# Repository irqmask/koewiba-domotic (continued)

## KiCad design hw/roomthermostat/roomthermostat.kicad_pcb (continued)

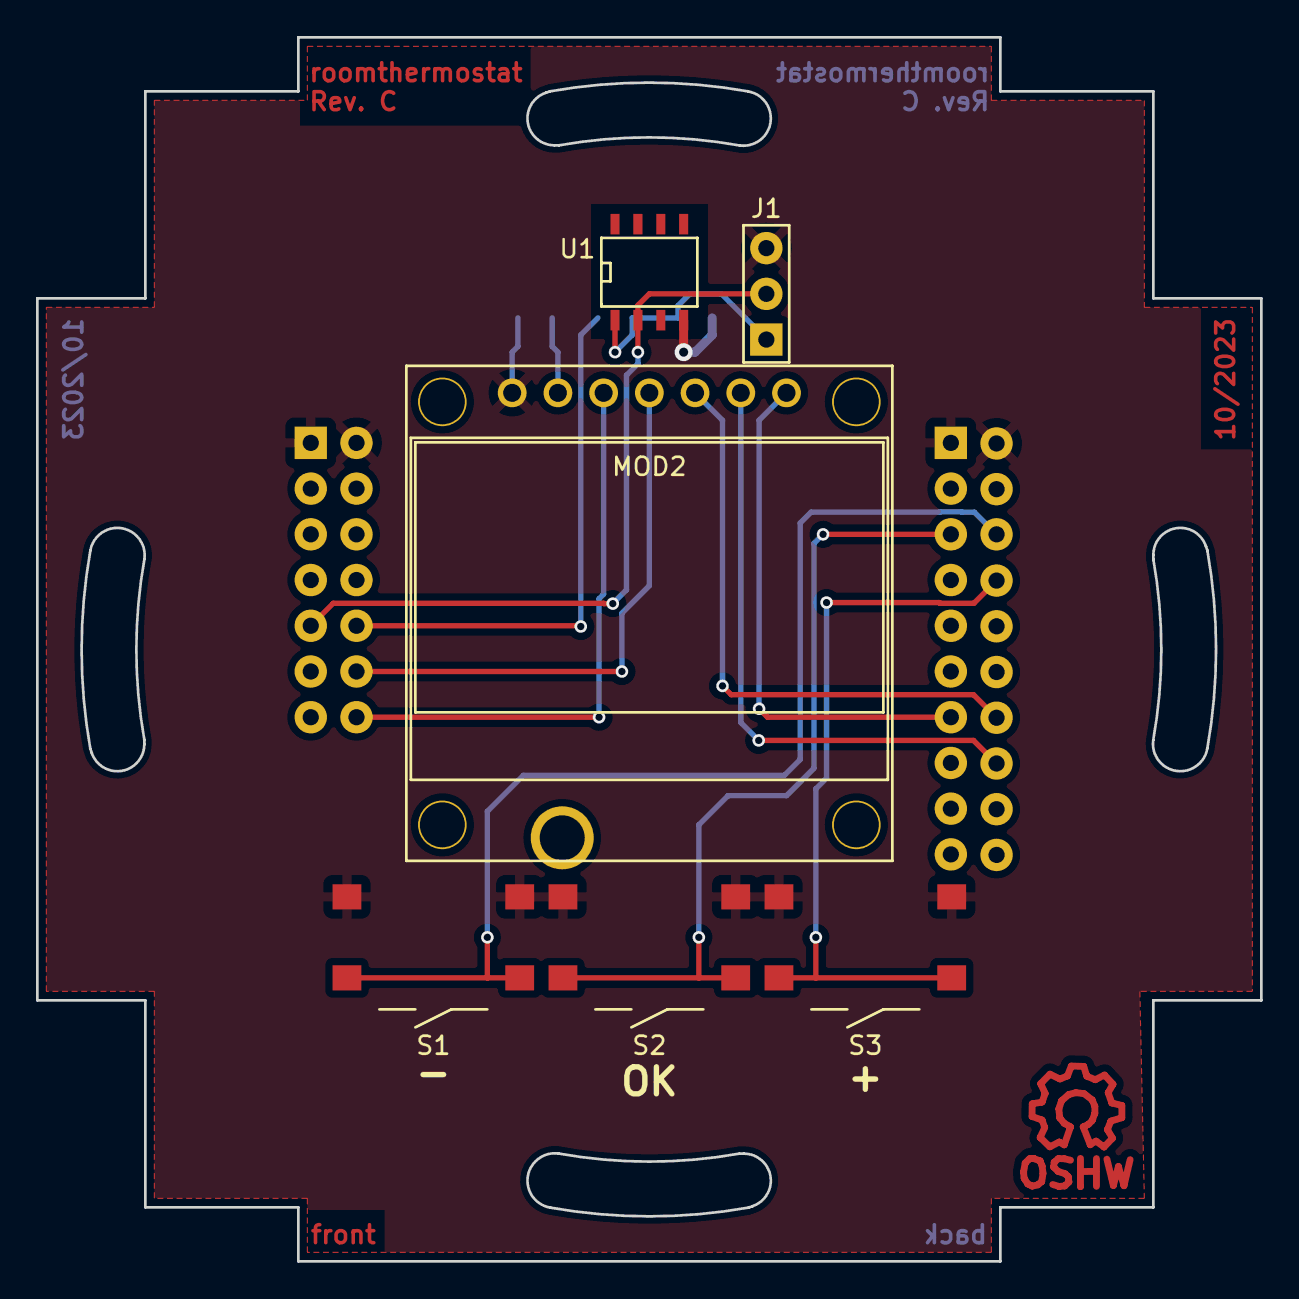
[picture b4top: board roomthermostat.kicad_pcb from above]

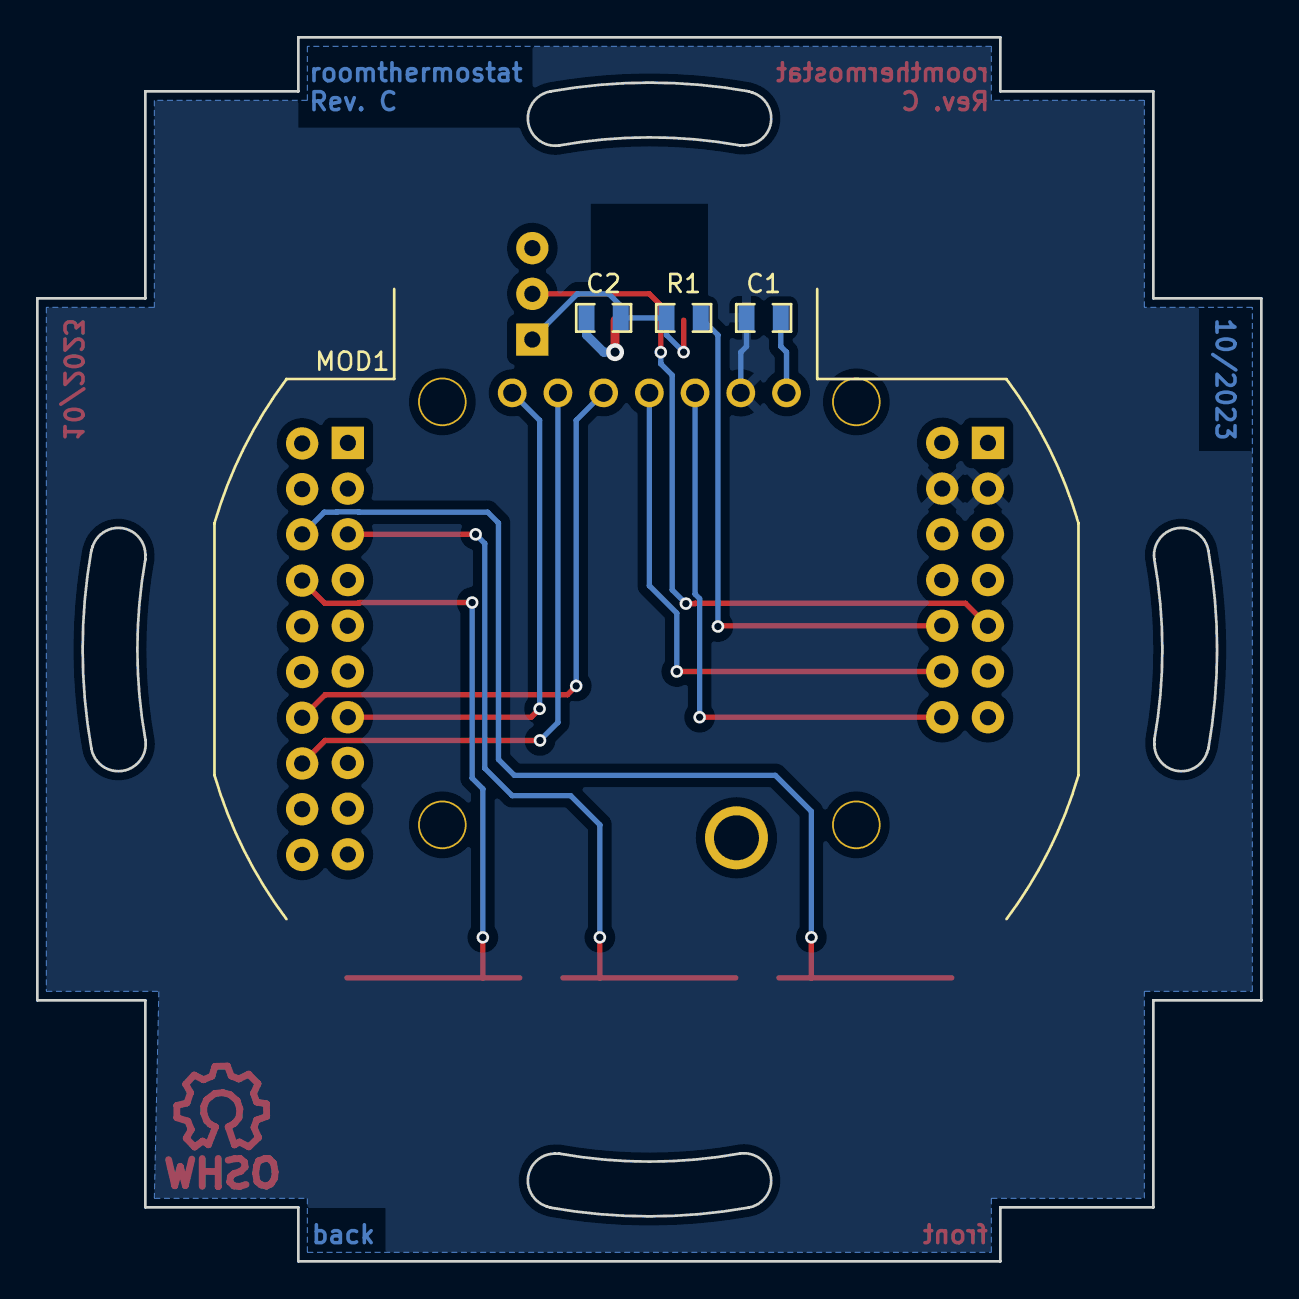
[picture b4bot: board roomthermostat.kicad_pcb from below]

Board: 2 copper layers, 68.0 x 68.0 mm, 11 parts (4 on the bottom side), 13 nets.

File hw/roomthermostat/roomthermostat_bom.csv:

"ID";"Bezeichner";"Gehäuse";"Stückzahl";"Bezeichnung";"Anbieter und Referenz";
1;"MOD2";"GraphDisplay_1_OLED_27x27,5mm_030072BA";1;"Graphic-OLED-Display_4wireSPI";;;
2;"U1";"SO8E";1;"TSIC206_SOIC8";;;
3;"S1,S2,S3";"PushButton_SPST_SMD_JTP-1138_BacksideMount";3;"PushButton_SPST_NO";;;
4;"LOGO1";"Symbol_OSHW-Logo_Copper";1;"OPEN_HARDWARE_1";;;
5;"J1";"HEADER_3x1";1;"CONN_3X1";;;
6;"C1,C2";"C_0805";2;"100nF";;;
7;"R1";"R_0805";1;"220";;;
8;"MOD1";"bus-module_atmega328";1;"bus-module_atmega328_revB";;;

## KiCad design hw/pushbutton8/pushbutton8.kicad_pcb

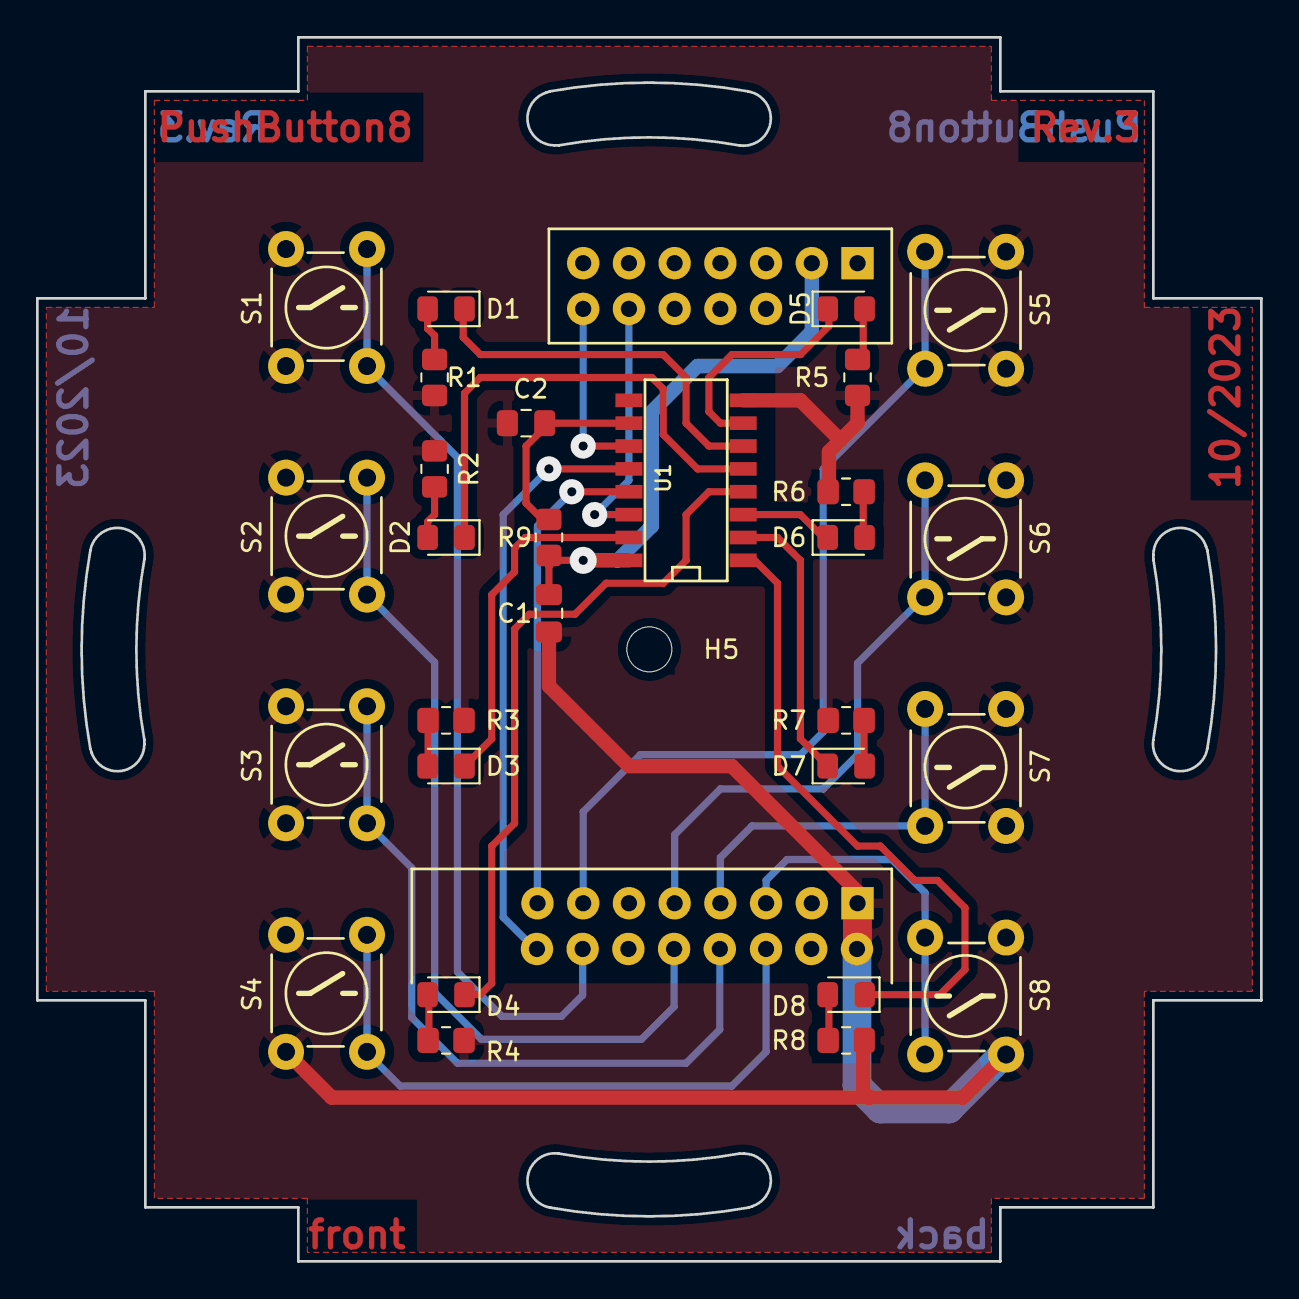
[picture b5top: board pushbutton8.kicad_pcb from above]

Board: 2 copper layers, 68.0 x 68.0 mm, 30 parts (1 on the bottom side), 31 nets.

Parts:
C1, C2: 100nF; C_0805_2012Metric_Pad1.18x1.45mm_HandSolder
D1, D2, D3, D4, D5, D6, D7, D8: LED; LED_0805_2012Metric_Pad1.15x1.40mm_HandSolder
H5: HOLE; MountingHole_2.5mm
MOD1: bus-module_atmega328
R1, R2, R3, R4, R5, R6, R7, R8: R; R_0805_2012Metric_Pad1.20x1.40mm_HandSolder
R9: 4k7; R_0805_2012Metric_Pad1.20x1.40mm_HandSolder
S1, S2, S3, S4, S5, S6, S7, S8: TASTER 3301; PHAP3301
U1: 74HC595; SO16N

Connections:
unnamed: C1.1, MOD1.23 (VCC), R9.1, U1.16 (VCC)
unnamed: C1.2, C2.2, MOD1.1 (GND), MOD1.2 (GND), R1.2, R2.2, R3.2, R4.2, R5.2, R6.2, R7.2, R8.2, S1.1, S2.1, S3.1, S4.1, S5.1, S6.1, S7.1, S8.1, U1.8 (GND)
unnamed: C2.1, R9.2, U1.10 (~MR)
unnamed: D1.1 (A), U1.6 (Q6)
unnamed: D1.2 (C), R1.1
unnamed: D2.1 (A), U1.5 (Q5)
unnamed: D2.2 (C), R2.1
unnamed: D3.1 (A), U1.15 (Q0)
unnamed: D3.2 (C), R3.1
unnamed: D4.1 (A), U1.4 (Q4)
unnamed: D4.2 (C), R4.1
unnamed: D5.1 (A), U1.7 (Q7)
unnamed: D5.2 (C), R5.1
unnamed: D6.1 (A), U1.3 (Q3)
unnamed: D6.2 (C), R6.1
unnamed: D7.1 (A), U1.2 (Q2)
unnamed: D7.2 (C), R7.1
unnamed: D8.1 (A), U1.1 (Q1)
unnamed: D8.2 (C), R8.1
unnamed: MOD1.5 (PC1), S8.2
unnamed: MOD1.6 (PC0), S4.2
unnamed: MOD1.7 (PC3), S7.2
unnamed: MOD1.8 (PC2), S3.2
unnamed: MOD1.9 (PC5), S6.2
unnamed: MOD1.10 (PC4), S2.2
unnamed: MOD1.13 (PD4), S5.2
unnamed: MOD1.14 (PD3), S1.2
unnamed: MOD1.15 (PD6), U1.13 (~OE)
unnamed: MOD1.16 (PD5), U1.12 (STCLK)
unnamed: MOD1.32 (MOSI), U1.14 (SER)
unnamed: MOD1.34 (SCK), U1.11 (SRCLK)

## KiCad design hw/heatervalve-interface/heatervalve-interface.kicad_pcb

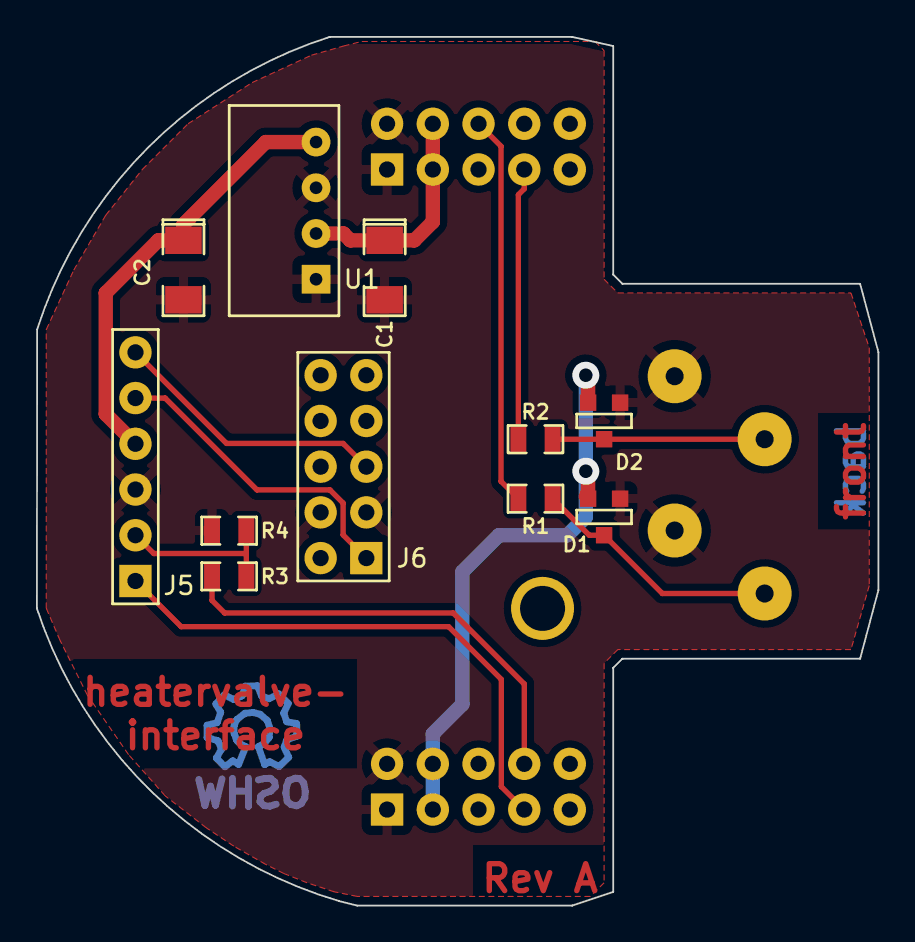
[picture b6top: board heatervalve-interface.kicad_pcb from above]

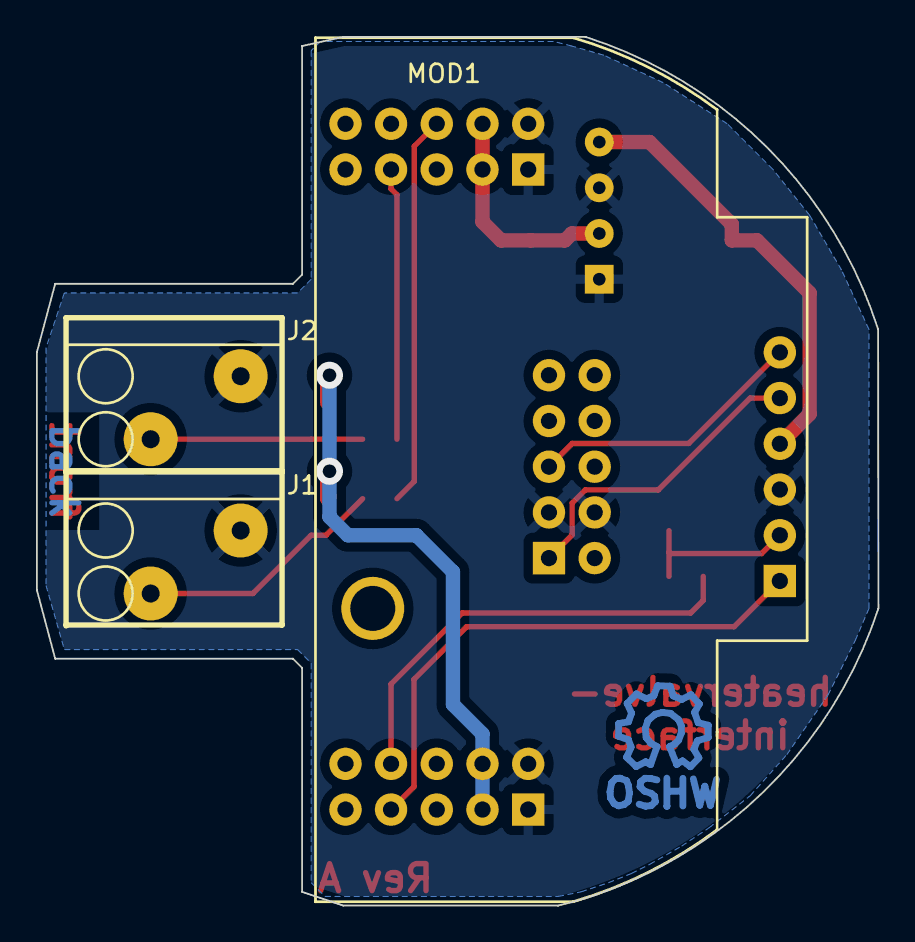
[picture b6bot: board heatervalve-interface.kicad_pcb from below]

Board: 2 copper layers, 46.8 x 48.3 mm, 15 parts (4 on the bottom side), 13 nets.

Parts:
C1: 470µF; CP_1206
C2: 100µF; CP_1206
D1, D2: BAT54S; SOT23-3
J1, J2: CONN_2X1; WAGO250-202
J5: CONN_6X1; HEADER_6x1
J6: CONN_5X2; HEADER_5x2
LOGO1: OPEN_HARDWARE_1; Symbol_OSHW-Logo_Copper
MOD1: bus-module_attiny1634_revB; bus-module_attiny1634
R1, R2, R3: 4k7; R_0805
R4: 9k1; R_0805
U1: AM1S-2403; AM1S-XXXX_SIL4

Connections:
+3.3V: C2.1, J5.4, U1.4 (VOUT+)
+5V: D1.2, D2.2, MOD1.13 (VCC), MOD1.14 (VCC)
+24V: C1.1, MOD1.3 (24V), MOD1.4 (24V), U1.2 (VIN+)
/RXD: J5.1, MOD1.17 (MISO)
/STM8_RST: J5.5, J6.1
/TXD: MOD1.18 (MOSI), R3.1
GND: C1.2, C2.2, D1.1, D2.1, J1.2, J2.2, J5.3, J6.3, J6.4, MOD1.1 (GND), MOD1.2 (GND), MOD1.11 (GND), MOD1.12 (GND), R4.1, U1.1 (VIN-), U1.3 (VOUT-)
unnamed: D1.3, J1.1, R1.1
unnamed: D2.3, J2.1, R2.1
unnamed: J5.2, R3.2, R4.2
unnamed: J5.6, J6.5
unnamed: MOD1.6 (PA1), R1.2
unnamed: MOD1.7 (PA2), R2.2

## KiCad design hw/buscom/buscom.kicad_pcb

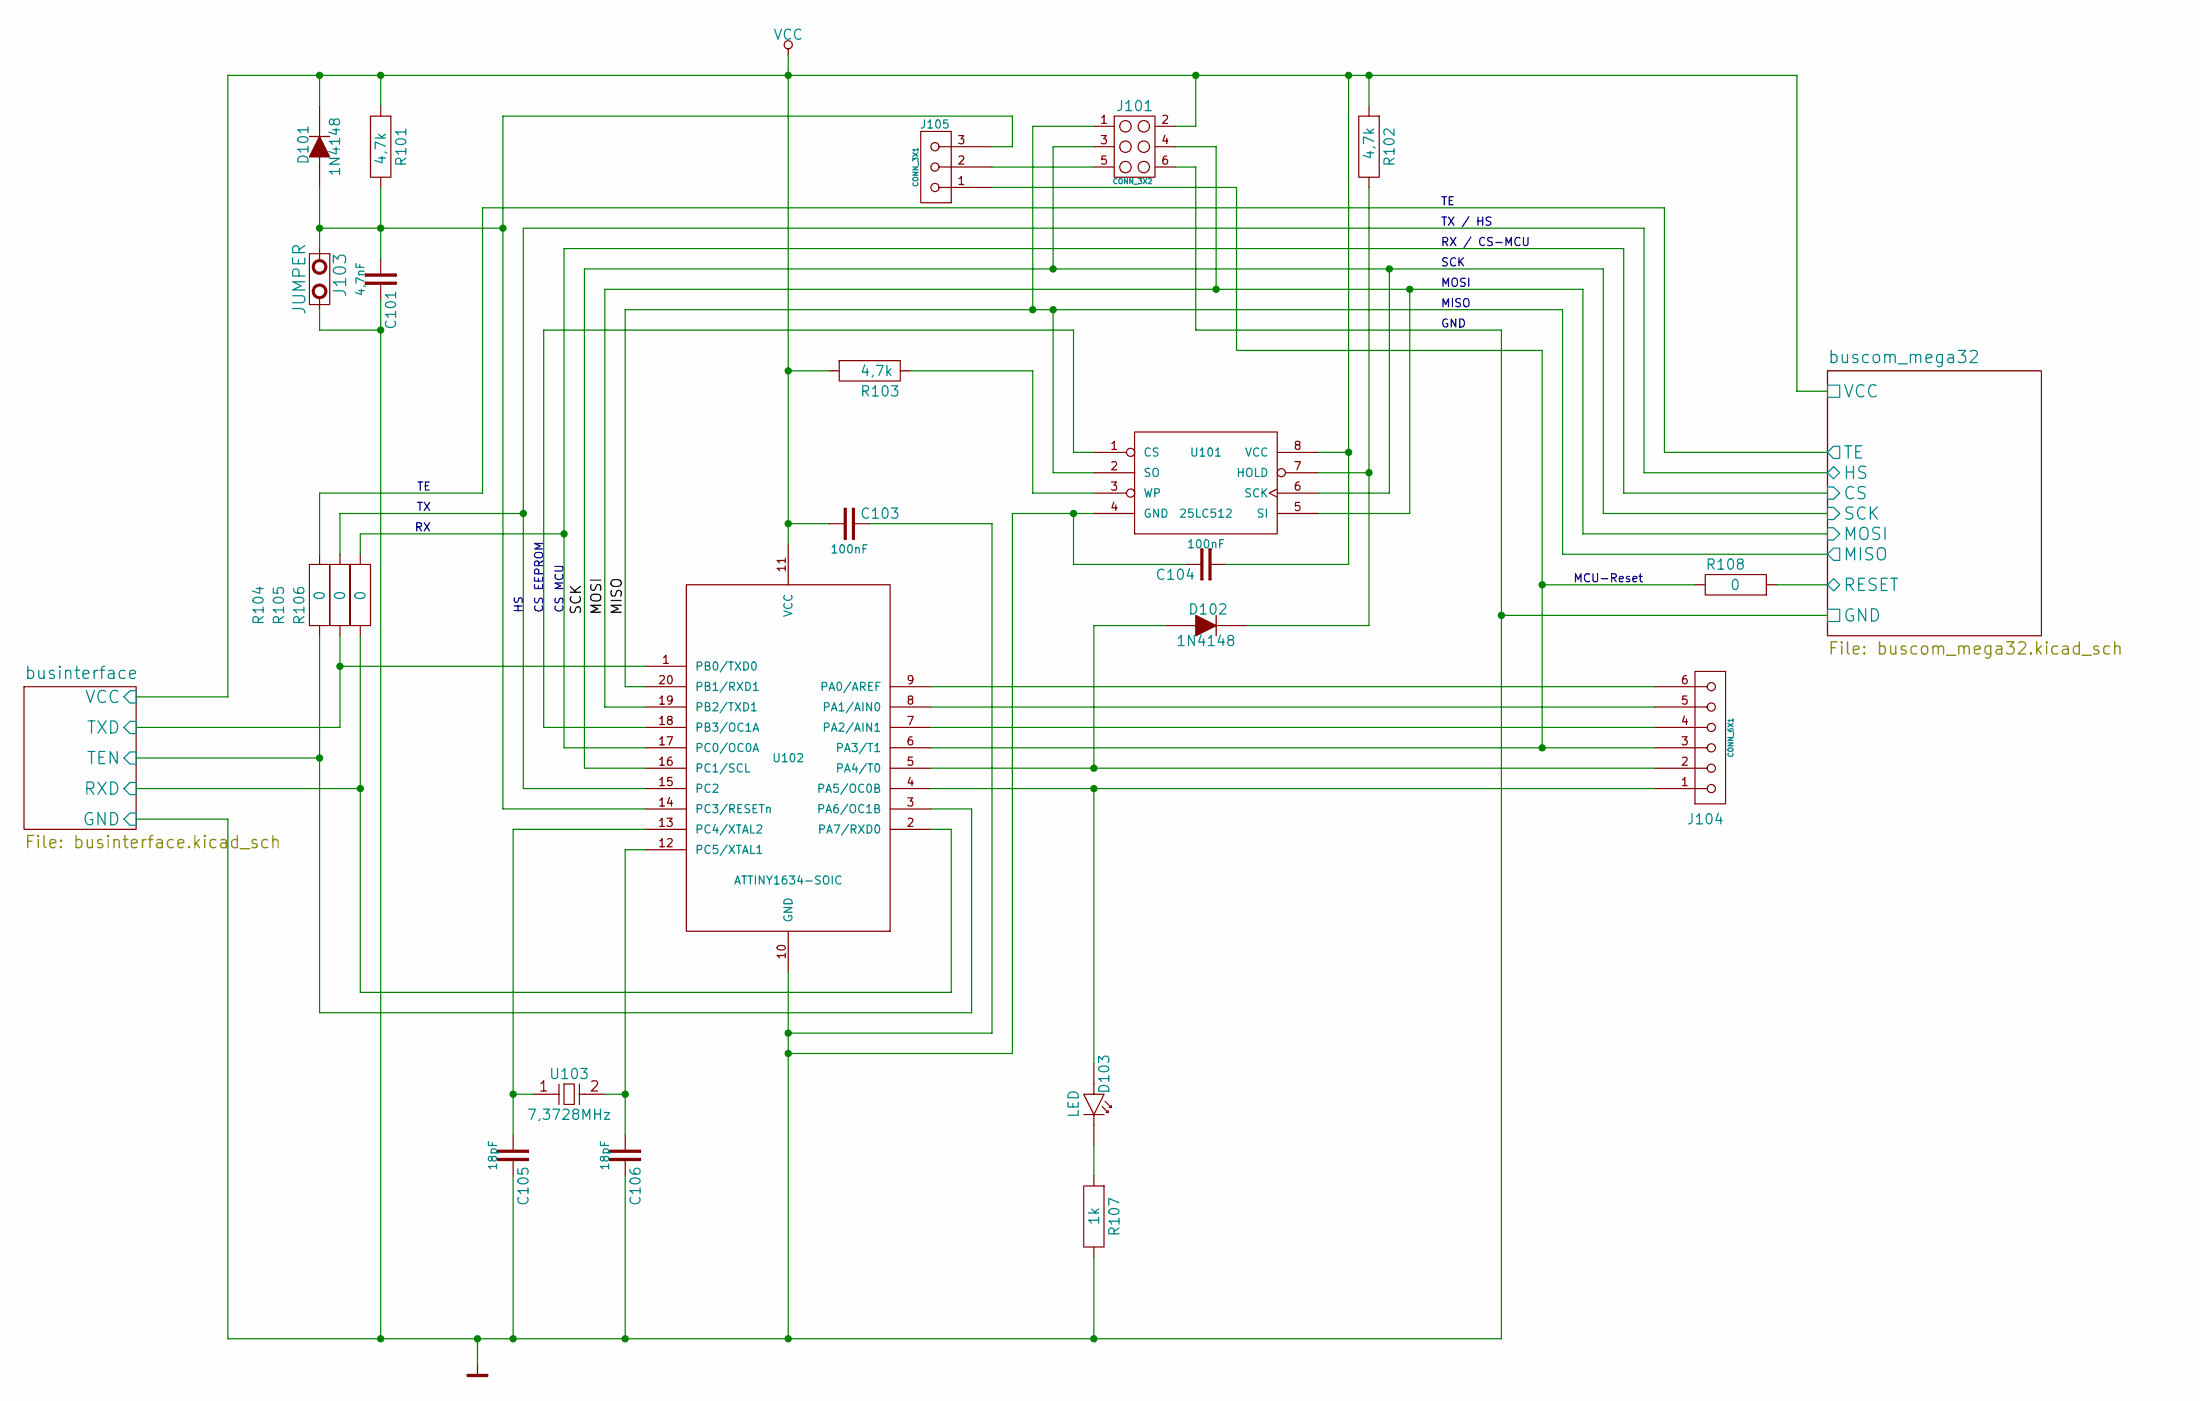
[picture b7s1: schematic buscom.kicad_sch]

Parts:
C101: 4,7nF
C103, C104: 100nF
C105, C106: 18pF
D101, D102: 1N4148
D103: LED
J101: CONN_3X2
J103: JUMPER
J104: CONN_6X1
J105: CONN_3X1
R101, R102, R103: 4,7k
R104, R105, R106, R108: 0
R107: 1k
U101: 25LC512; SO8N
U102: ATTINY1634-SOIC; SO20L
U103: 7,3728MHz

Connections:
/buscom_1: C101.2, C103.2, C104.2, C105.2, C106.2, J101.6, J103.2, R107.2, U101.4 (GND), U102.10 (GND); also elsewhere on the board
/buscom_3: R108.1; also elsewhere on the board
/buscom_7: J101.1, U101.2 (SO), U102.20 (PB1/RXD1); also elsewhere on the board
/buscom_8: J101.3, U101.6 (SCK), U102.16 (PC1/SCL); also elsewhere on the board
/buscom_9: J101.4, U101.5 (SI), U102.19 (PB2/TXD1); also elsewhere on the board
/buscom_36: R104.1; also elsewhere on the board
/buscom_37: R105.1, U102.15 (PC2); also elsewhere on the board
/buscom_38: R106.1, U102.17 (PC0/OC0A); also elsewhere on the board
/businte2: C103.1, C104.1, D101.2 (C), J101.2, R101.1, R102.1, R103.1, U101.8 (VCC), U102.11 (VCC); also elsewhere on the board
/businte42: R104.2, U102.3 (PA6/OC1B); also elsewhere on the board
/businte43: R105.2, U102.1 (PB0/TXD0); also elsewhere on the board
/businte44: R106.2, U102.2 (PA7/RXD0); also elsewhere on the board
unnamed: J101.5, J105.2
unnamed: J104.3, J105.1, R108.2, U102.6 (PA3/T1)
unnamed: D102.1 (A), J104.2, U102.5 (PA4/T0)
unnamed: U101.1 (CS), U102.18 (PB3/OC1A)
unnamed: C106.1, U102.12 (PC5/XTAL1), U103.2
unnamed: J104.6, U102.9 (PA0/AREF)
unnamed: J104.5, U102.8 (PA1/AIN0)
unnamed: J104.4, U102.7 (PA2/AIN1)
unnamed: D102.2 (C), R102.2, U101.7 (HOLD)
unnamed: R103.2, U101.3 (WP)
unnamed: D103.2 (C), R107.1
unnamed: D103.1 (A), J104.1, U102.4 (PA5/OC0B)
unnamed: C101.1, D101.1 (A), J103.1, J105.3, R101.2, U102.14 (PC3/RESETn)
unnamed: C105.1, U102.13 (PC4/XTAL2), U103.1

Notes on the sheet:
CS EEPROM
MOSI
SCK
MCU-Reset
CS MCU
GND
MISO
RX / CS-MCU
TX / HS

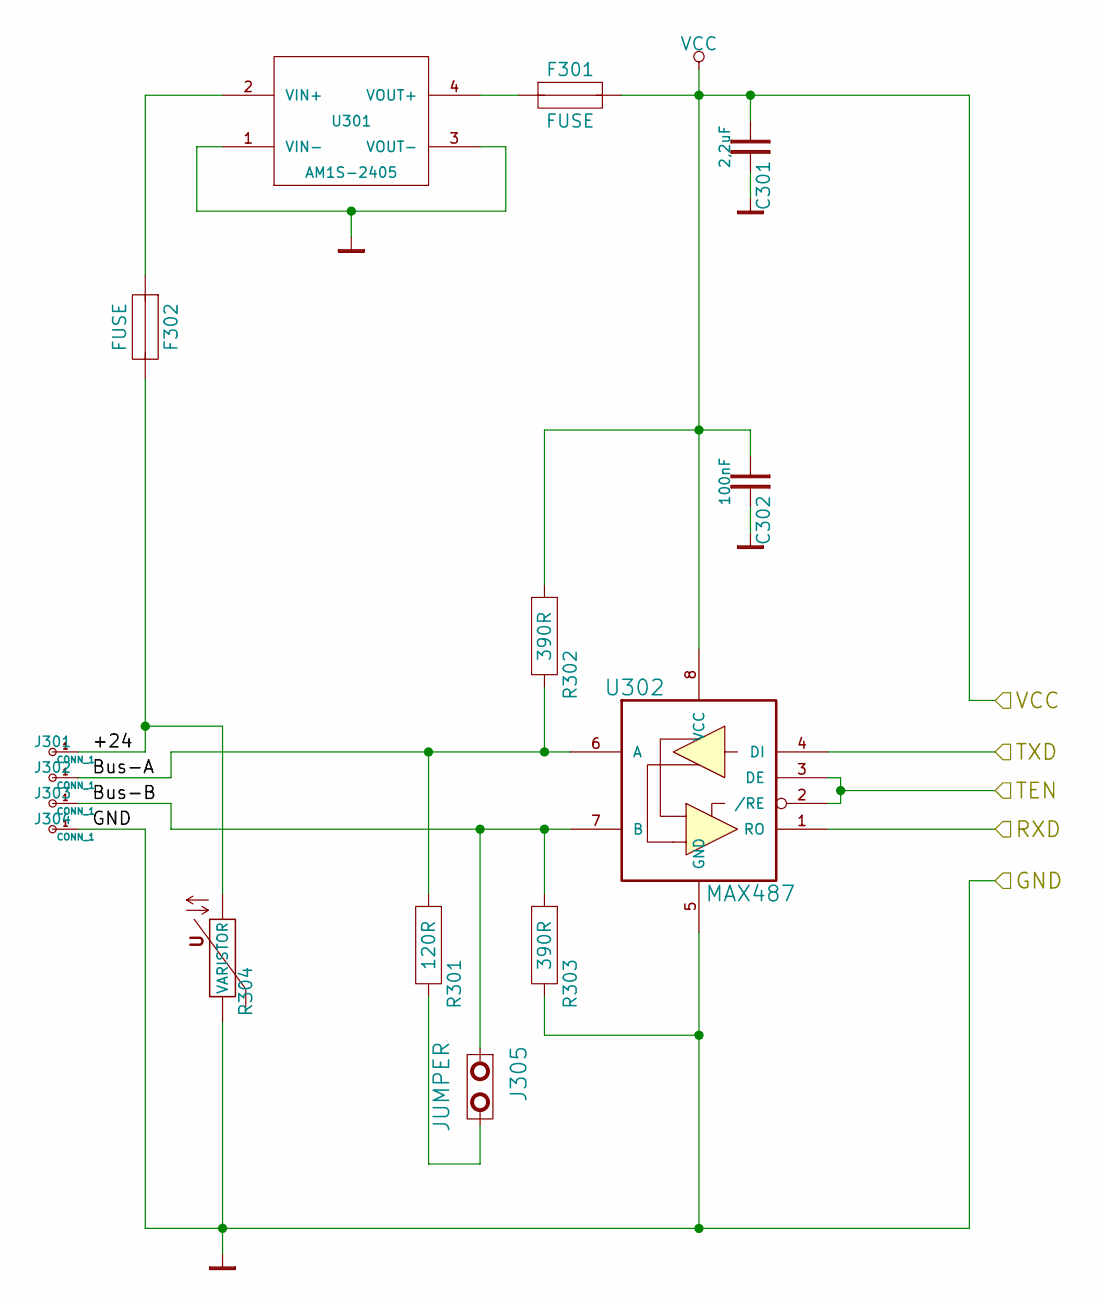
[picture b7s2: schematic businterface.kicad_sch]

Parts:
C301: 2,2uF
C302: 100nF
F301, F302: FUSE
J301, J302, J303, J304: CONN_1
J305: JUMPER
R301: 120R
R302, R303: 390R
R304: VARISTOR
U301: AM1S-2405; MODULE
U302: MAX487; SSOP28

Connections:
/buscom_1: C301.2, C302.2, J304.1, R303.2, R304.1, U301.1 (VIN-), U301.3 (VOUT-), U302.5 (GND); also elsewhere on the board
/businte2: C301.1, C302.1, F301.2, R302.1, U302.8 (VCC); also elsewhere on the board
/businte6: F302.2, J301.1, R304.2
/businte40: J302.1, R301.1, R302.2, U302.6 (A)
/businte41: J303.1, J305.1, R303.1, U302.7 (B)
/businte42: U302.2 (/RE), U302.3 (DE); also elsewhere on the board
/businte43: U302.4 (DI); also elsewhere on the board
/businte44: U302.1 (RO); also elsewhere on the board
unnamed: F302.1, U301.2 (VIN+)
unnamed: F301.1, U301.4 (VOUT+)
unnamed: J305.2, R301.2

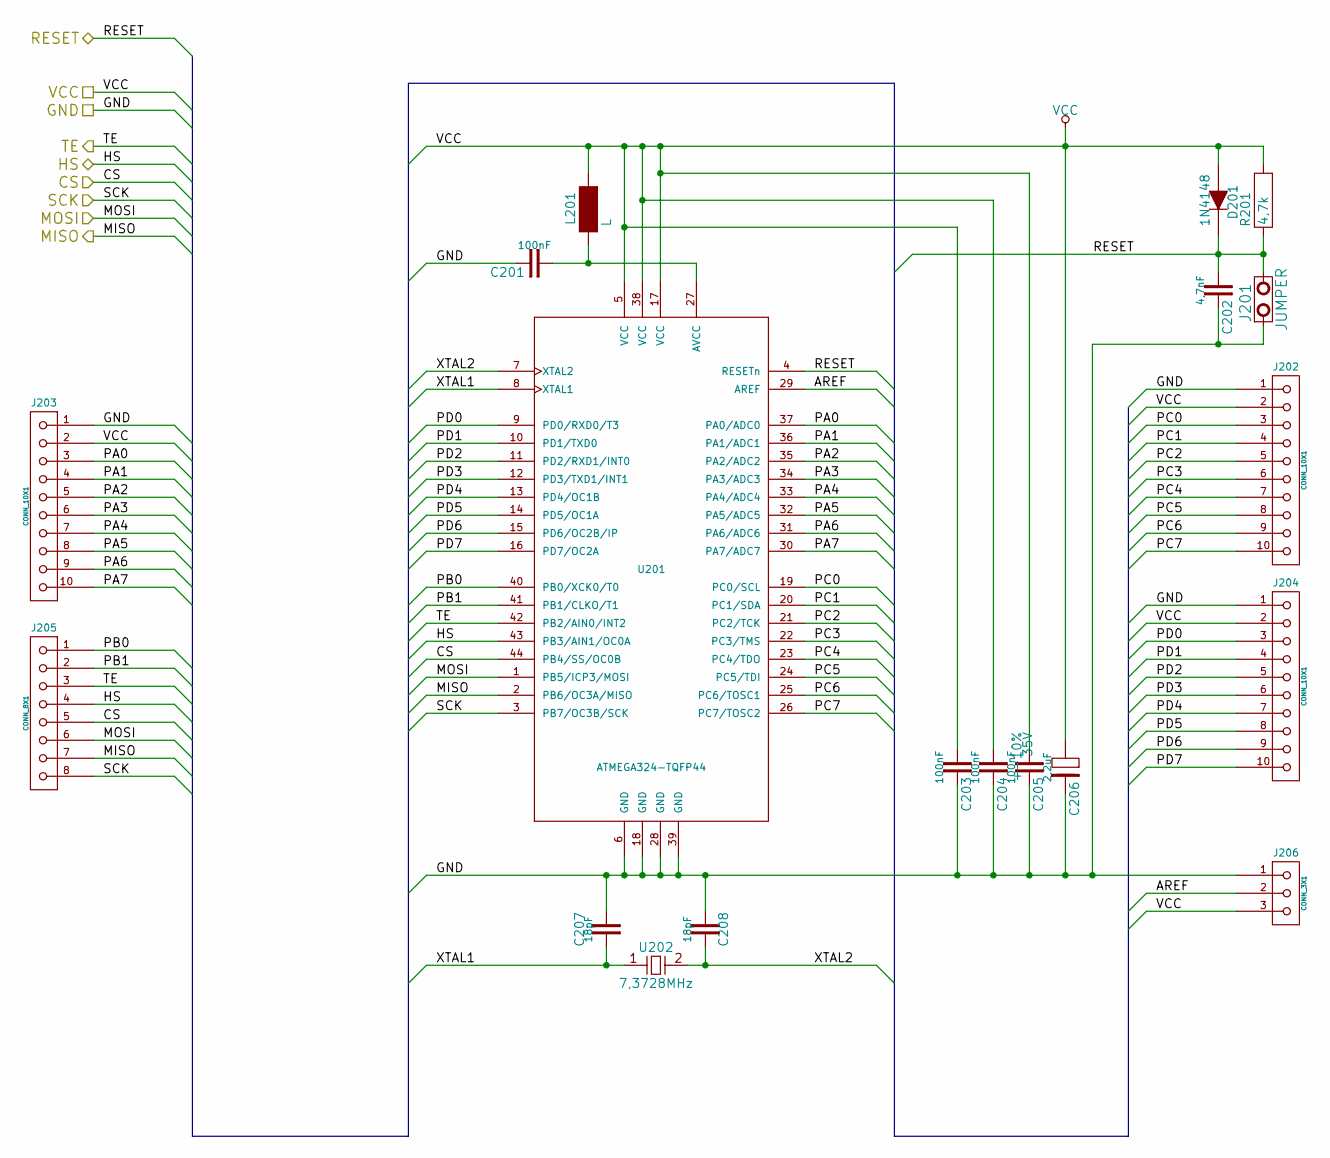
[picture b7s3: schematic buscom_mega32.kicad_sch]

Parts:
C201, C203, C204, C205: 100nF
C202: 4,7nF
C206: 2,2uF; 35V
C207, C208: 18pF
D201: 1N4148
J201: JUMPER
J202, J203, J204: CONN_10X1
J205: CONN_8X1
J206: CONN_3X1
L201: L
R201: 4,7k
U201: ATMEGA324-TQFP44; TQFP44
U202: 7,3728MHz

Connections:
/buscom_1: C201.2, C202.2, C203.2, C204.2, C205.2, C206.2, C207.1, C208.1, J201.1, J202.1, J203.1, J204.1, J206.1, U201.6 (GND), U201.18 (GND), U201.28 (GND), U201.39 (GND); also elsewhere on the board
/buscom_3: C202.1, D201.2 (C), J201.2, R201.2, U201.4 (RESETn); also elsewhere on the board
/buscom_4: C207.2, U201.8 (XTAL1), U202.1
/buscom_5: C208.2, U201.7 (XTAL2), U202.2
/buscom_7: J205.7, U201.2 (PB6/OC3A/MISO); also elsewhere on the board
/buscom_8: J205.8, U201.3 (PB7/OC3B/SCK); also elsewhere on the board
/buscom_9: J205.6, U201.1 (PB5/ICP3/MOSI); also elsewhere on the board
/buscom_10: J202.3, U201.19 (PC0/SCL)
/buscom_11: J202.4, U201.20 (PC1/SDA)
/buscom_12: J202.5, U201.21 (PC2/TCK)
/buscom_13: J202.6, U201.22 (PC3/TMS)
/buscom_14: J202.7, U201.23 (PC4/TDO)
/buscom_15: J202.8, U201.24 (PC5/TDI)
/buscom_16: J202.9, U201.25 (PC6/TOSC1)
/buscom_17: J202.10, U201.26 (PC7/TOSC2)
/buscom_18: J203.3, U201.37 (PA0/ADC0)
/buscom_19: J203.4, U201.36 (PA1/ADC1)
/buscom_20: J203.5, U201.35 (PA2/ADC2)
/buscom_21: J203.6, U201.34 (PA3/ADC3)
/buscom_22: J203.7, U201.33 (PA4/ADC4)
/buscom_23: J203.8, U201.32 (PA5/ADC5)
/buscom_24: J203.9, U201.31 (PA6/ADC6)
/buscom_25: J203.10, U201.30 (PA7/ADC7)
/buscom_26: J204.3, U201.9 (PD0/RXD0/T3)
/buscom_27: J204.4, U201.10 (PD1/TXD0)
/buscom_28: J204.5, U201.11 (PD2/RXD1/INT0)
/buscom_29: J204.6, U201.12 (PD3/TXD1/INT1)
/buscom_30: J204.7, U201.13 (PD4/OC1B)
/buscom_31: J204.8, U201.14 (PD5/OC1A)
/buscom_32: J204.9, U201.15 (PD6/OC2B/IP)
/buscom_33: J204.10, U201.16 (PD7/OC2A)
/buscom_34: J205.1, U201.40 (PB0/XCK0/T0)
/buscom_35: J205.2, U201.41 (PB1/CLKO/T1)
/buscom_36: J205.3, U201.42 (PB2/AIN0/INT2); also elsewhere on the board
/buscom_37: J205.4, U201.43 (PB3/AIN1/OC0A); also elsewhere on the board
/buscom_38: J205.5, U201.44 (PB4/SS/OC0B); also elsewhere on the board
/buscom_39: J206.2, U201.29 (AREF)
/businte2: C203.1, C204.1, C205.1, C206.1, D201.1 (A), J202.2, J203.2, J204.2, J206.3, L201.1, R201.1, U201.5 (VCC), U201.17 (VCC), U201.38 (VCC); also elsewhere on the board
unnamed: C201.1, L201.2, U201.27 (AVCC)

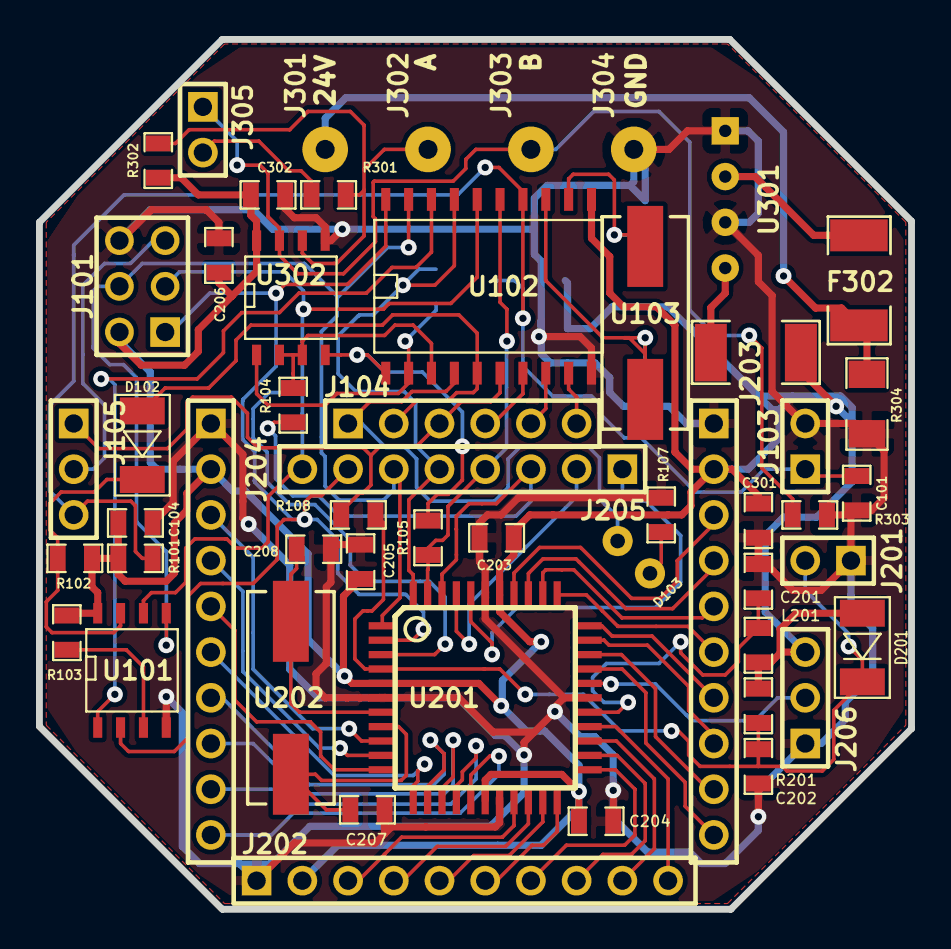
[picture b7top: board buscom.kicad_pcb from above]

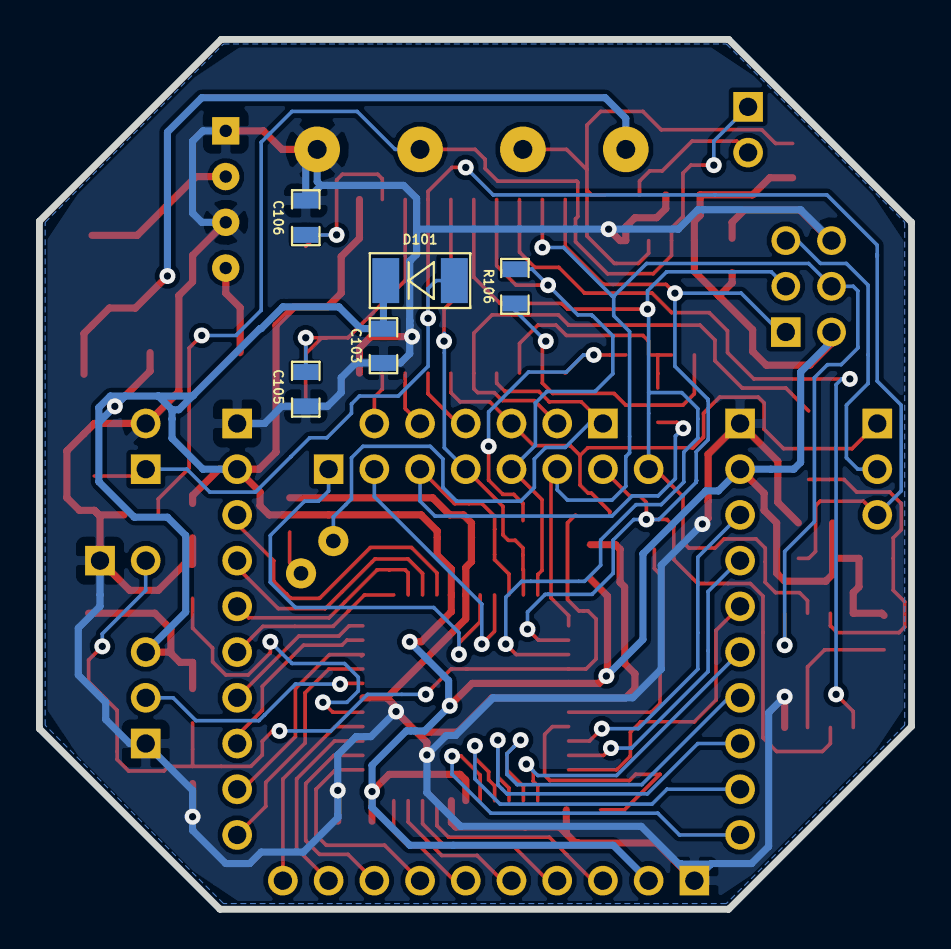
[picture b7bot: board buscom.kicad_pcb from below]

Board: 2 copper layers, 48.5 x 48.3 mm, 57 parts (5 on the bottom side), 62 nets.
